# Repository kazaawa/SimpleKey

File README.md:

# SimpleKey

必要最低限の機能を持った分離型キーボードです。
ファームウェアの書き込みはsrc内のsimplekeyをqmk_firmware\keyboardsに入れて実行してください。

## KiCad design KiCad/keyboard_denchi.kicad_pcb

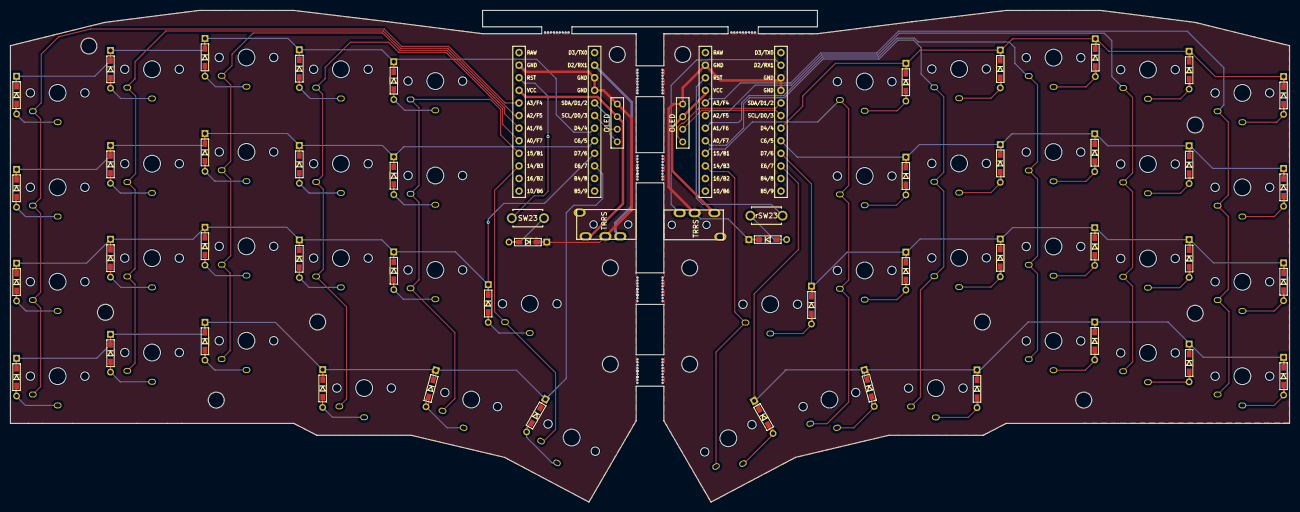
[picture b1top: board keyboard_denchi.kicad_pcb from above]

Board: 2 copper layers, 258.1 x 99.2 mm, 98 parts (0 on the bottom side), 76 nets.

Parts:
D1, D2, D3, D4, D5, D6, D7, D8, D9, D10, D11, D12, D13, D14, D15, D16, D17, D18, D19, D20, D21, D22, D23: D; D3_TH_SMD
J1: MJ-4PP-9; TRRS_PJ-320A
OL1: OLED
SW1, SW2, SW3, SW4, SW5, SW6, SW7, SW8, SW9, SW10, SW11, SW12, SW13, SW14, SW15, SW16, SW17, SW18, SW19, SW20, SW21, SW22: SW_PUSH; Kailh_Choc_V1
SW23: SW_PUSH; SW_PUSH_6x3mm
U1: ProMicro; ProMicro_r
rD1, rD2, rD3, rD4, rD5, rD6, rD7, rD8, rD9, rD10, rD11, rD12, rD13, rD14, rD15, rD16, rD17, rD18, rD19, rD20, rD21, rD22, rD23: D; D3_TH_SMD
rJ1: MJ-4PP-9; TRRS_PJ-320A
rOL1: OLED
rSW1, rSW2, rSW3, rSW4, rSW5, rSW6, rSW7, rSW8, rSW9, rSW10, rSW11, rSW12, rSW13, rSW14, rSW15, rSW16, rSW17, rSW18, rSW19, rSW20, rSW21, rSW22: SW_PUSH; Kailh_Choc_V1
rSW23: SW_PUSH; SW_PUSH_6x3mm
rU1: ProMicro; ProMicro_r

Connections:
GND: D23.1 (K), J1.C, OL1.4 (GND), U1.3 (GND), U1.4 (GND), U1.23 (GND), rD23.1 (K), rJ1.C, rOL1.4 (GND), rU1.3 (GND), rU1.4 (GND), rU1.23 (GND)
unnamed: D1.2 (A), SW1.2
unnamed: D2.2 (A), SW2.2
unnamed: D3.2 (A), SW3.2
unnamed: D4.2 (A), SW4.2
unnamed: D5.2 (A), SW5.2
unnamed: D6.2 (A), SW6.2
unnamed: D7.2 (A), SW7.2
unnamed: D8.2 (A), SW8.2
unnamed: D9.2 (A), SW9.2
unnamed: D10.2 (A), SW10.2
unnamed: D11.2 (A), SW11.2
unnamed: D12.2 (A), SW12.2
unnamed: D13.2 (A), SW13.2
unnamed: D14.2 (A), SW14.2
unnamed: D15.2 (A), SW15.2
unnamed: D16.2 (A), SW16.2
unnamed: D17.2 (A), SW17.2
unnamed: D18.2 (A), SW18.2
unnamed: D19.2 (A), SW19.2
unnamed: D20.2 (A), SW20.2
unnamed: D21.2 (A), SW21.2
unnamed: D22.2 (A), SW22.2
unnamed: D23.2 (A), SW23.2
unnamed: rD1.2 (A), rSW1.2
unnamed: rD2.2 (A), rSW2.2
unnamed: rD3.2 (A), rSW3.2
unnamed: rD4.2 (A), rSW4.2
unnamed: rD5.2 (A), rSW5.2
unnamed: rD6.2 (A), rSW6.2
unnamed: rD7.2 (A), rSW7.2
unnamed: rD8.2 (A), rSW8.2
unnamed: rD9.2 (A), rSW9.2
unnamed: rD10.2 (A), rSW10.2
unnamed: rD11.2 (A), rSW11.2
unnamed: rD12.2 (A), rSW12.2
unnamed: rD13.2 (A), rSW13.2
unnamed: rD14.2 (A), rSW14.2
unnamed: rD15.2 (A), rSW15.2
unnamed: rD16.2 (A), rSW16.2
unnamed: rD17.2 (A), rSW17.2
unnamed: rD18.2 (A), rSW18.2
unnamed: rD19.2 (A), rSW19.2
unnamed: rD20.2 (A), rSW20.2
unnamed: rD21.2 (A), rSW21.2
unnamed: rD22.2 (A), rSW22.2
unnamed: rD23.2 (A), rSW23.2
VCC: J1.D, OL1.3 (VCC), U1.21 (VCC), rJ1.D, rOL1.3 (VCC), rU1.21 (VCC)
col0: SW1.1, SW6.1, SW11.1, SW17.1, U1.20 (F4/A3)
col1: SW2.1, SW7.1, SW12.1, SW18.1, U1.19 (F5/A2)
col2: SW3.1, SW8.1, SW13.1, SW19.1, U1.18 (F6/A1)
col3: SW4.1, SW9.1, SW14.1, SW20.1, U1.17 (F7/A0)
col4: SW5.1, SW10.1, SW15.1, SW21.1, U1.16 (B1/15)
col5: SW16.1, SW22.1, U1.15 (B3/14)
data: J1.B, U1.2 (RX1/D2)
rcol0: rSW1.1, rSW6.1, rSW11.1, rSW17.1, rU1.20 (F4/A3)
rcol1: rSW2.1, rSW7.1, rSW12.1, rSW18.1, rU1.19 (F5/A2)
rcol2: rSW3.1, rSW8.1, rSW13.1, rSW19.1, rU1.18 (F6/A1)
rcol3: rSW4.1, rSW9.1, rSW14.1, rSW20.1, rU1.17 (F7/A0)
rcol4: rSW5.1, rSW10.1, rSW15.1, rSW21.1, rU1.16 (B1/15)
rcol5: rSW16.1, rSW22.1, rU1.15 (B3/14)
rdata: rJ1.B, rU1.2 (RX1/D2)
reset: SW23.1, U1.22 (RST)
row0: D1.1 (K), D2.1 (K), D3.1 (K), D4.1 (K), D5.1 (K), U1.7 (4/D4)
row1: D6.1 (K), D7.1 (K), D8.1 (K), D9.1 (K), D10.1 (K), U1.8 (5/C6)
row2: D11.1 (K), D12.1 (K), D13.1 (K), D14.1 (K), D15.1 (K), D16.1 (K), U1.9 (6/D7)
row3: D17.1 (K), D18.1 (K), D19.1 (K), D20.1 (K), D21.1 (K), D22.1 (K), U1.10 (7/E6)
rreset: rSW23.1, rU1.22 (RST)
rrow0: rD1.1 (K), rD2.1 (K), rD3.1 (K), rD4.1 (K), rD5.1 (K), rU1.7 (4/D4)
rrow1: rD6.1 (K), rD7.1 (K), rD8.1 (K), rD9.1 (K), rD10.1 (K), rU1.8 (5/C6)
rrow2: rD11.1 (K), rD12.1 (K), rD13.1 (K), rD14.1 (K), rD15.1 (K), rD16.1 (K), rU1.9 (6/D7)
rrow3: rD17.1 (K), rD18.1 (K), rD19.1 (K), rD20.1 (K), rD21.1 (K), rD22.1 (K), rU1.10 (7/E6)
rscl: rOL1.2 (SCL), rU1.6 (3/D0/SCL)
rsda: rOL1.1 (SDA), rU1.5 (2/D1/SDA)
scl: OL1.2 (SCL), U1.6 (3/D0/SCL)
sda: OL1.1 (SDA), U1.5 (2/D1/SDA)

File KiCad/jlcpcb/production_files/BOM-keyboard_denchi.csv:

Comment,Designator,Footprint,LCSC
D,D9,D3_TH_SMD,
SW_PUSH,rSW21,Kailh_Choc_V1,
D,D1,D3_TH_SMD,
D,rD8,D3_TH_SMD,
D,rD11,D3_TH_SMD,
D,rD19,D3_TH_SMD,
SW_PUSH,SW5,Kailh_Choc_V1,
SW_PUSH,rSW18,Kailh_Choc_V1,
SW_PUSH,SW9,Kailh_Choc_V1,
D,rD1,D3_TH_SMD,
D,rD2,D3_TH_SMD,
D,D18,D3_TH_SMD,
ProMicro,rU1,ProMicro_r,
D,rD21,D3_TH_SMD,
SW_PUSH,rSW12,Kailh_Choc_V1,
SW_PUSH,rSW17,Kailh_Choc_V1,
D,D6,D3_TH_SMD,
SW_PUSH,SW6,Kailh_Choc_V1,
D,D13,D3_TH_SMD,
D,D19,D3_TH_SMD,
D,D8,D3_TH_SMD,
SW_PUSH,rSW10,Kailh_Choc_V1,
SW_PUSH,rSW3,Kailh_Choc_V1,
D,D20,D3_TH_SMD,
OLED,rOL1,OLED,
D,rD7,D3_TH_SMD,
SW_PUSH,SW18,Kailh_Choc_V1,
D,rD17,D3_TH_SMD,
MJ-4PP-9,J1,TRRS_PJ-320A,
SW_PUSH,rSW20,Kailh_Choc_V1,
SW_PUSH,rSW11,Kailh_Choc_V1,
D,rD3,D3_TH_SMD,
D,rD15,D3_TH_SMD,
D,D21,D3_TH_SMD,
SW_PUSH,rSW13,Kailh_Choc_V1,
SW_PUSH,SW21,Kailh_Choc_V1,
SW_PUSH,SW14,Kailh_Choc_V1,
ProMicro,U1,ProMicro_r,
D,D15,D3_TH_SMD,
D,D10,D3_TH_SMD,
D,rD18,D3_TH_SMD,
SW_PUSH,rSW1,Kailh_Choc_V1,
D,D16,D3_TH_SMD,
SW_PUSH,rSW19,Kailh_Choc_V1,
D,D2,D3_TH_SMD,
MJ-4PP-9,rJ1,TRRS_PJ-320A,
SW_PUSH,SW16,Kailh_Choc_V1,
D,D23,D3_TH_SMD,
SW_PUSH,SW12,Kailh_Choc_V1,
SW_PUSH,rSW15,Kailh_Choc_V1,
SW_PUSH,rSW8,Kailh_Choc_V1,
SW_PUSH,SW7,Kailh_Choc_V1,
D,rD10,D3_TH_SMD,
SW_PUSH,rSW23,SW_PUSH_6x3mm,
D,rD22,D3_TH_SMD,
D,D3,D3_TH_SMD,
D,D11,D3_TH_SMD,
SW_PUSH,rSW7,Kailh_Choc_V1,
SW_PUSH,rSW2,Kailh_Choc_V1,
SW_PUSH,SW8,Kailh_Choc_V1,
D,rD13,D3_TH_SMD,
D,rD20,D3_TH_SMD,
SW_PUSH,SW2,Kailh_Choc_V1,
SW_PUSH,rSW9,Kailh_Choc_V1,
SW_PUSH,SW15,Kailh_Choc_V1,
D,D17,D3_TH_SMD,
SW_PUSH,SW13,Kailh_Choc_V1,
SW_PUSH,rSW22,Kailh_Choc_V1,
D,rD6,D3_TH_SMD,
D,rD9,D3_TH_SMD,
SW_PUSH,rSW5,Kailh_Choc_V1,
SW_PUSH,SW4,Kailh_Choc_V1,
SW_PUSH,SW17,Kailh_Choc_V1,
D,rD14,D3_TH_SMD,
SW_PUSH,rSW6,Kailh_Choc_V1,
D,D22,D3_TH_SMD,
SW_PUSH,SW10,Kailh_Choc_V1,
SW_PUSH,SW23,SW_PUSH_6x3mm,
SW_PUSH,rSW4,Kailh_Choc_V1,
D,rD12,D3_TH_SMD,
D,D5,D3_TH_SMD,
SW_PUSH,SW22,Kailh_Choc_V1,
SW_PUSH,SW1,Kailh_Choc_V1,
D,D14,D3_TH_SMD,
D,D4,D3_TH_SMD,
D,rD23,D3_TH_SMD,
SW_PUSH,SW3,Kailh_Choc_V1,
D,D7,D3_TH_SMD,
SW_PUSH,SW19,Kailh_Choc_V1,
SW_PUSH,rSW16,Kailh_Choc_V1,
D,rD4,D3_TH_SMD,
D,rD5,D3_TH_SMD,
D,D12,D3_TH_SMD,
SW_PUSH,rSW14,Kailh_Choc_V1,
SW_PUSH,SW20,Kailh_Choc_V1,
D,rD16,D3_TH_SMD,
SW_PUSH,SW11,Kailh_Choc_V1,
OLED,OL1,OLED,

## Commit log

2025-01-15 add qmk src
2025-01-30 add kicad data
2025-05-10 コンパイル済みhexファイル
2025-05-14 Rename keymap.c to keymap(old).c
2025-05-16 config.c の更新
2025-05-16 rules.mk の更新
2025-05-26 config.h の作成
2025-05-26 config.h の更新
2025-05-29 Add files via upload
    config.cの削除
    keymaps/defaultにconfig.hを作成し編集
    rules.mkの編集
